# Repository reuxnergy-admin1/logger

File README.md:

# StratusLog

KiCad project for the StratusLog environmental data logger:

- ATmega1284P-A MCU (Arduino-style, 3.3 V)
- DS3231M RTC + CR2032 backup
- microSD storage (Hirose DM3AT)
- LSM100A LoRa/Sigfox modem (SMA antenna)
- SDI-12 transceiver (SN74LVC1G240 + BSS123)
- LT1372HVCS8 5 V→12 V boost for sensor power
- 3× Phoenix MKDS-1-7-3.81 sensor terminals

## Documentation

- **[docs/REVIEW_AND_VALVE_DRIVER.md](docs/REVIEW_AND_VALVE_DRIVER.md)** — schematic review with prioritized findings + valve driver add-on (latching + non-latching).
- **`valves.kicad_sch`** — starter hierarchical sub-sheet for the valve driver block.

## Open priorities (see review doc)

1. Boost converter (U4) — add inductor, Schottky, output cap, FB divider, compensation.
2. 3.3 V regulator — currently missing from the BOM.
3. AVR ISP header — currently no path to flash the bootloader.
4. Crystal Y1 — set frequency (8 MHz @ 3.3 V) and footprint; add load caps.
5. Resistors — change 0201 footprint to 0603 to match HandSolder intent.

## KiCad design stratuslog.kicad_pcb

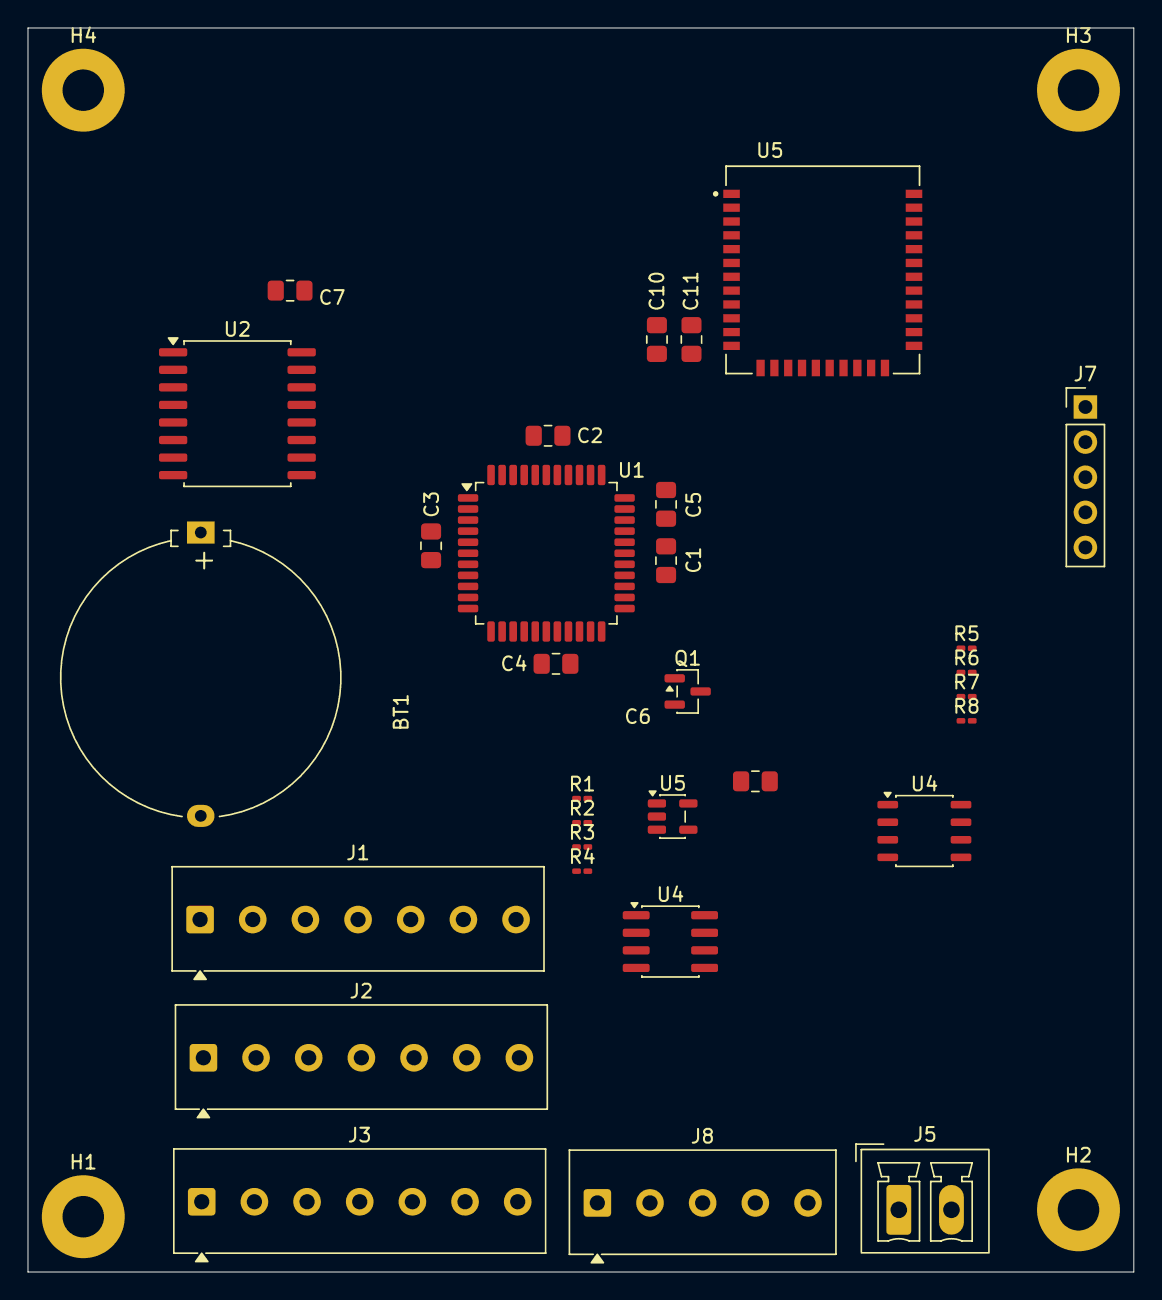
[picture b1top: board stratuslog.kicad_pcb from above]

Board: 4 copper layers, 80.0 x 90.0 mm, 36 parts (1 on the bottom side), 27 nets, no tracks yet.

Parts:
BT1: Battery_Cell; Battery_Panasonic_CR2032-HFN_Horizontal_CircularHoles
C1, C2, C3, C4, C5, C6, C7, C11: 100n; C_0805_2012Metric_Pad1.18x1.45mm_HandSolder
C10: 10u; C_0805_2012Metric_Pad1.18x1.45mm_HandSolder
H1, H2, H3, H4: MountingHole_Pad; MountingHole_3mm_Pad
J1, J2, J3: Conn_01x07_Pin; TerminalBlock_Phoenix_MKDS-1-7-3.81_1x07_P3.81mm_Horizontal
J4: Micro_SD_Card; microSD_HC_Hirose_DM3AT-SF-PEJM5
J5: Conn_01x02_Pin; PhoenixContact_MCV_1,5_2-G-3.81_1x02_P3.81mm_Vertical
J7: Conn_01x05_Pin; PinHeader_1x05_P2.54mm_Vertical
J8: Conn_01x05_Pin; TerminalBlock_Phoenix_MKDS-1-5-3.81_1x05_P3.81mm_Horizontal
Q1: BSS123; SOT-23
R1, R4: 47k; R_0201_0603Metric_Pad0.64x0.40mm_HandSolder
R2, R3: 510R; R_0201_0603Metric_Pad0.64x0.40mm_HandSolder
R5, R6: 1k; R_0201_0603Metric_Pad0.64x0.40mm_HandSolder
R7, R8: 4.7k; R_0201_0603Metric_Pad0.64x0.40mm_HandSolder
U1: ATmega1284P-A; TQFP-44_10x10mm_P0.8mm
U2: DS3231M; SOIC-16W_7.5x10.3mm_P1.27mm
U4: GD25D10CT; JEITA_SOIC-8_3.9x4.9mm_P1.27mm
U4#2: LT1372HVCS8; SOIC-8_3.9x4.9mm_P1.27mm
U5: LSM100A; XCVR_LSM100A
U5#2: MCP1662-xOT; SOT-23-5

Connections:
+3V3: C1.1, C2.1, C3.1, C4.1, C7.1, C10.2, C11.2, J4.4 (VDD), R1.1, R4.2, R7.1, R8.1, U1.5 (VCC), U1.17 (VCC), U1.27 (AVCC), U1.38 (VCC), U5.11 (VDD)
/3V3: J2.4, J3.4, J7.4
/12VOUT: J3.5, J3.6
/A0: J1.1, U1.37 (PA0)
/A1: J1.2, U1.36 (PA1)
/A2: J1.3, U1.35 (PA2)
/A3: J1.4, U1.34 (PA3)
/A4: J1.5, U1.33 (PA4)
/AREF: C5.1, J1.6, J1.7, U1.29 (AREF)
/BOOT_LSM: U1.30 (PA7), U5.31 (BOOT)
/CLK: J7.2, U5.8 (PA14/SWCLK)
/DIO: J7.1, U5.7 (PA13/SWDIO)
/MISO: J4.7 (DAT0), U1.2 (PB6)
/RST: J7.5, U5.30 (~RST)
/SCL: R7.2, U1.19 (PC0), U2.16 (SCL)
/SDA: R8.2, U1.20 (PC1), U2.15 (SDA)
/SDI-12: J3.7, R3.2
/UART_RX: Q1.3 (D), R1.2, U1.10 (PD1)
/UART_RX_1: U1.12 (PD3), U5.14 (PA2/UART2_TX)
/UART_TX_1: U1.11 (PD2), U5.13 (PA3/UART2_RX)
/VIN: C6.1, J5.1, U4#2.5 (Vin)
/WAKE: U1.40 (PB0), U5.16 (PA0/BUT1)
GND: BT1.2 (-), C1.2, C2.2, C3.2, C4.2, C5.2, C6.2, C7.2, C10.1, C11.1, J2.6, J2.7, J3.1, J3.2, J4.6 (VSS), J4.SH (SHIELD), J5.2, J7.3, J8.2, J8.4, J8.5, Q1.2 (S), R5.2, R6.2, U1.6 (GND), U1.18 (GND), U1.28 (GND), U1.39 (GND), U2.5 (GND), U2.6 (GND), U2.7 (GND), U2.8 (GND), U2.9 (GND), U2.10 (GND), U2.11 (GND), U2.12 (GND), U2.13 (GND), U4#2.6 (GNDS), U4#2.7 (GND), U5.1 (GND), U5.10 (GND), U5.12 (GND), U5.20 (GND), U5.23 (GND), U5.32 (GND), U5.34 (GND)
unnamed: BT1.1 (+), U2.14 (VBAT)
unnamed: R2.2, R3.1
unnamed: J4.2 (DAT3/CD), R4.1
unnamed: Q1.1 (G), R2.1

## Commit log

2026-05-29 Add design review and valve driver sub-sheet
    - docs/REVIEW_AND_VALVE_DRIVER.md: prioritized review of stratuslog.kicad_sch
    covering boost completion, missing 3V3 LDO, no AVR ISP, crystal value,
    0201 vs HandSolder mismatch, SDI-12 protection, and field hardening
    - valves.kicad_sch: starter hierarchical sub-sheet with hierarchical labels
    for 12VOUT, GND, V1_IN1, V1_IN2, V2_EN, V3_EN, V_PWR_EN; populate per doc
    - README.md: project overview and pointer to review doc
2026-05-29 Add programming-header (ISP + FTDI) section and fix Port A TQFP pin numbers
2026-05-29 Add tipping-bucket pulse-input circuit (PB2/INT2/PCINT10) section
2026-05-31 Add SDI-12 interface review: VIN power, LVC vs 3.3V levels, floating /OE, 7.5V Zener
